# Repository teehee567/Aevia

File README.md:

# Aevia

Aevia is a DIY, battery powered lap timer and track data logger. The current hardware is the V2 Mini, a compact board that combines multi-band GNSS, a 6-axis IMU, local storage, a display interface, physical controls, and wireless connectivity.

Uses very very high end sensors, UM980, SCH16T-K01

The goal is to build something in the same general space as a Garmin Catalyst, but at a lower cost and with more control over the hardware, raw data, and software. Recorded data should also remain useful outside the device, with export to proper desktop analysis tools.

## V2 Mini hardware

The V2 Mini is built around:

- `ESP32-S31-WROOM-3-N16R16V` as the main processor and radio
- `UM980` multi-band, multi-constellation GNSS receiver
- `SCH16T-K01-1` 6-axis accelerometer and gyroscope
- microSD storage over 4-bit SDIO
- a 24-pin SPI display interface for the Adafruit 4520
- four UI buttons and four RGB status LEDs
- native USB data and USB-C power
- a 1-cell battery charger, fuel gauge, and push-button power control

See [v2_mini_design.md](./v2_mini_design.md) for the block diagrams, power tree, fitted parts, and current one-off build estimate.

## Firmware and software plan

The [base firmware](./firmware/README.md) provides structured hardware bring-up
and a button-free J6 USB inactive-slot updater. Build from `firmware/` with
`cargo build --release --locked`; use the host decoder and `board_check.py` to
upload an application image and retain its diagnostics. The
[evaluation procedure](./firmware/docs/evaluation.md) gives the repeatable
stationary bench, USB fault and recovery checks.

The immediate work is hardware bring-up and the basic firmware needed to read the GNSS and IMU, store sessions on the microSD card, and exercise the display and controls. The application backlog currently looks like this.

### High priority

- [ ] Delta T lap timing with colour coding
- [ ] Raw-data analysis that can support lap times reported to 0.001 seconds and show the limits of the hardware
- [ ] Export to Harry's LapTimer or another tool that accepts the recorded data

### Medium priority

- [ ] G-G diagram, with filtering suitable for noisy IMU output
- [ ] Automatic track detection
  - [ ] Track learning mode
  - [ ] Manual start and finish line setup
- [ ] Smart battery management
- [ ] Theoretical best lap time
- [ ] Automatic recording based on acceleration
- [ ] Sector splits for tracks that support them

### Low priority

- [ ] Configurable LED bar
- [ ] Customisable gauges
- [ ] Colour themes

### Stretch ideas

- [ ] CAN bus or OBD data logging for brake, throttle, and other vehicle data
- [ ] Bluetooth support through the ESP32
  - [ ] RTK corrections, with a target of roughly 50 Hz and centimetre-level positioning
  - [ ] Firmware updates over Bluetooth
- [ ] Action camera synchronisation

## Why the UM980

Of the modules considered, the UM980 is the best fit I found for raw GNSS quality at this price. It can output at 20 Hz while using multiple GNSS constellations. That matters in a car because an antenna inside the windscreen loses much of its view behind the metal roof. Combining GPS, GLONASS, Galileo, and BeiDou leaves more satellites available for each fix and can improve accuracy when the view of the sky is limited. A receiver advertised as "multi-GNSS" does not necessarily support its maximum update rate while using several constellations at once.

It also supports multiple frequency bands. A single-band receiver has a harder time separating a direct signal from one reflected by the car or nearby barriers. Comparing L1 with L2 or L5 gives the receiver more information for rejecting poor measurements.

The planned BT-T076 is a wide multi-band active helical antenna, although its sheet does not explicitly document every UM980 signal. Helical designs generally tolerate tilt and an uncertain ground plane better than conventional patches, but the BT-T076 datasheet does not publish the angular, per-band patterns needed to rank it against a particular patch. A correctly integrated patch that covers every required band may provide cleaner measurements in a fixed installation; many common patches are only L1 or depend on a specific ground plane. See [the GNSS antenna decision note](./gnss_antenna_design.md) for the mounting scenarios, electrical constraints, expected data effects, and A/B test plan.

The expected gain over a decent off-the-shelf logger is not enormous, and software quality will matter just as much as the receiver. For absolute lap-time proof, a track transponder still wins.

### Receivers considered

These figures are working notes from the module research and should be checked again before buying parts.

| Receiver | Notes |
|---|---|
| Unicore `UM980` | L1, L2/L5, and L6; multi-constellation; full RTK; 20 Hz with full multi-GNSS; about 50 Hz in RTK mode; roughly A$130 |
| u-blox `NEO-M9N` | L1-only; multi-constellation; 25 Hz with one constellation or 10 Hz with several; roughly A$20 |
| u-blox `NEO-M10S` | L1-only; multi-constellation; 25 Hz with one constellation or 10 Hz with several; roughly A$20 |
| u-blox `ZED-F9P` | L1 and L2; multi-constellation; full RTK; about 8 Hz with everything enabled or 20 Hz with a reduced configuration; roughly A$130 |
| Quectel `LC29H-DA/EA` | L1 and L5; multi-constellation; RTK on the EA variant; 10 Hz maximum |
| Septentrio `mosaic-X5` | All bands and constellations; the best raw quality in this comparison; capable of 100 Hz; more than A$1,000 |
| SkyTraq `PX1122R` | L1 and L2; multi-constellation RTK; apparently up to 20 Hz, although documentation and pricing were difficult to find |

The Dragy Pro was the only off-the-shelf product for which I could identify the receiver module. It uses a u-blox NEO-M10S and is listed in the research as 10 Hz with multiple constellations or 20 Hz with one. I have not found a module that clearly delivers 25 Hz, multi-GNSS, and 10 cm accuracy at the same time, so similar product claims are unlikely to be real.

The longer comparison is in [data/gps_module_research.md](./data/gps_module_research.md).
And raw GNSS modules specs are in [data/GNSS_research.xlsx](./data/GNSS_research.xlsx).

## Repository map

- [V2 Mini design notes](./v2_mini_design.md)
- [GNSS helix-versus-patch and dashboard placement analysis](./gnss_antenna_design.md)
- [V2 Mini KiCad project](./hardware/v2_mini_pcb/v2_mini.kicad_pro)
- [V2 Mini root schematic](./hardware/v2_mini_pcb/v2_mini.kicad_sch)
- [V2 Mini PCB layout](./hardware/v2_mini_pcb/v2_mini.kicad_pcb)
- [V2 Mini production BOM](./hardware/v2_mini_pcb/production/digikey_bom.csv)
- [GNSS module research](./data/gps_module_research.md)
- [V1 PCB files](./hardware/v1_pcb/)
- [Earlier full-size V2 design notes](./v2_design.md)

## Building it

I do not recommend this as a first electronics build. Several parts need reflow equipment or a capable hot-air setup, and a one off board involves a fair amount of tooling and rework cost. The V2 Mini estimate is about $500AUD for the PCB, stencil, parts, GNSS receiver, antenna, and battery.

## V1 archive

archive, old, bad

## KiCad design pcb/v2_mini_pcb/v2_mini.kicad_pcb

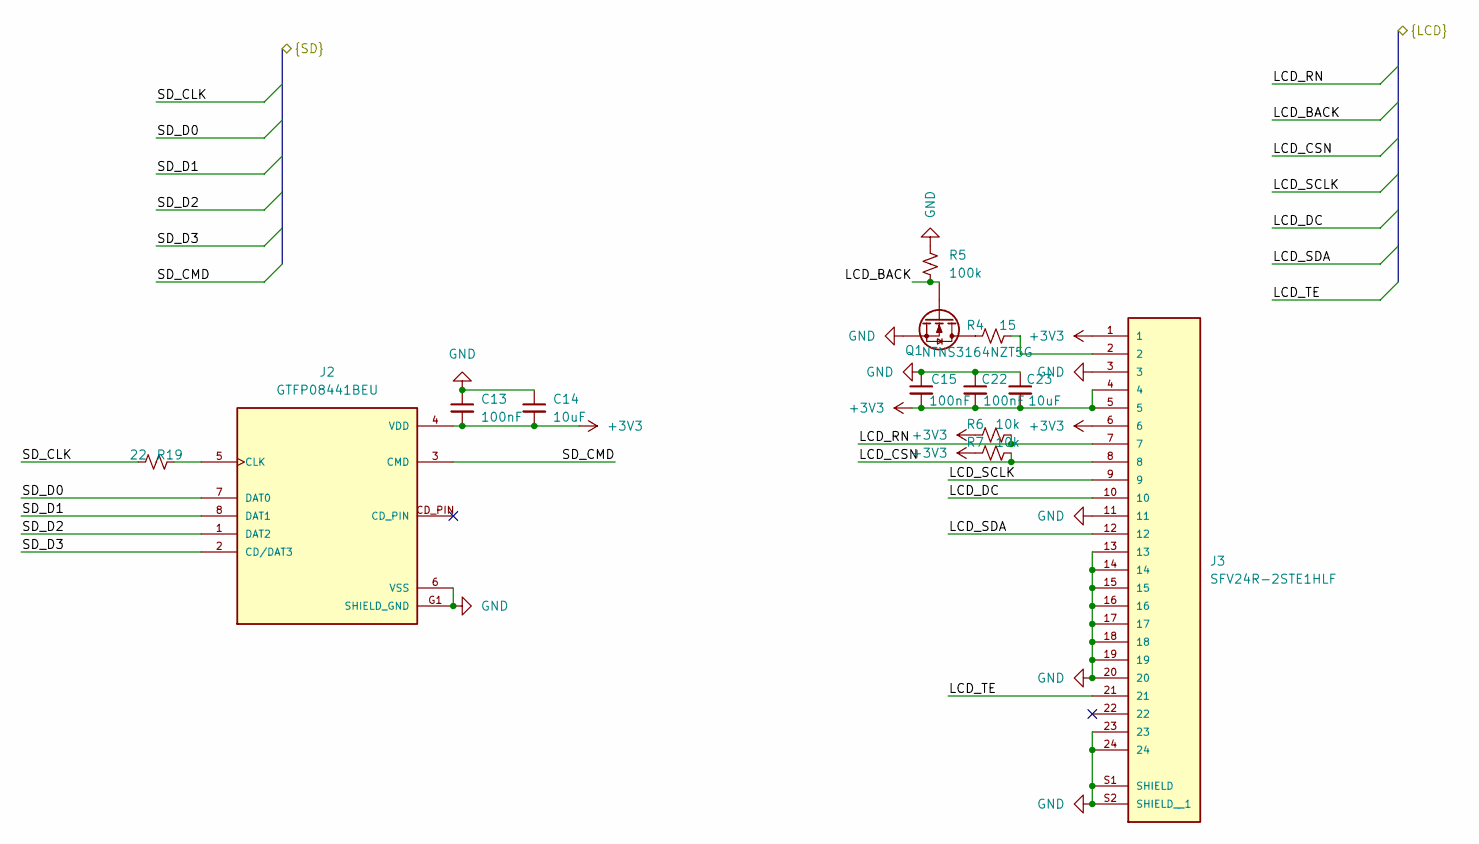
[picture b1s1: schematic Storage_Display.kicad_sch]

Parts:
C13, C15, C22: 100nF; C_0402_1005Metric; Voltage 16V; Tolerance 10%; MPN CL05B104KO5NNNC; LCSC C1525
C14, C23: 10uF; C_0603_1608Metric; Voltage 10V; Tolerance 10%; MPN CL10A106KP8NNND; DigiKey_PN 1276-CL10A106KP8NNNDCT-ND
J2: GTFP08441BEU; AMPHENOL_GTFP08441BEU; PARTREV F
J3: SFV24R-2STE1HLF; AMPHENOL_SFV24R-2STE1HLF; PARTREV C
Q1: NTNS3164NZT5G; SOT-883; MPN NTNS3164NZT5G
R4: 15; R_0402_1005Metric; MPN RC0402FR-0715RL
R5: 100k; R_0402_1005Metric; Voltage 50V; Tolerance 1%; MPN RC0402FR-07100KL; DigiKey_PN 311-100KLRCT-ND
R6, R7: 10k; R_0402_1005Metric; Voltage 50V; Tolerance 1%; MPN RC0402FR-0710KL; DigiKey_PN 311-10.0KLRCT-ND
R19: 22; R_0402_1005Metric; Voltage 50V; Tolerance 1%; MPN RC0402FR-0722RL; DigiKey_PN 311-22.0LRCT-ND

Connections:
+3V3: C13.2, C14.2, C15.2, C22.2, C23.2, J2.4 (VDD), J3.1, J3.4, J3.5, J3.6, R6.1, R7.1; also elsewhere on the board
/ESP32-S31 MCU/LCD_BACK: Q1.1 (G), R5.2; also elsewhere on the board
/ESP32-S31 MCU/LCD_CSN: J3.8, R7.2; also elsewhere on the board
/ESP32-S31 MCU/LCD_DC: J3.10; also elsewhere on the board
/ESP32-S31 MCU/LCD_RN: J3.7, R6.2; also elsewhere on the board
/ESP32-S31 MCU/LCD_SCLK: J3.9; also elsewhere on the board
/ESP32-S31 MCU/LCD_SDA: J3.12; also elsewhere on the board
/ESP32-S31 MCU/LCD_TE: J3.21; also elsewhere on the board
/ESP32-S31 MCU/SD_CLK: R19.1; also elsewhere on the board
/ESP32-S31 MCU/SD_CMD: J2.3 (CMD); also elsewhere on the board
/ESP32-S31 MCU/SD_D0: J2.7 (DAT0); also elsewhere on the board
/ESP32-S31 MCU/SD_D1: J2.8 (DAT1); also elsewhere on the board
/ESP32-S31 MCU/SD_D2: J2.1 (DAT2); also elsewhere on the board
/ESP32-S31 MCU/SD_D3: J2.2 (CD/DAT3); also elsewhere on the board
GND: C13.1, C14.1, C15.1, C22.1, C23.1, J2.6 (VSS), J2.G1 (SHIELD_GND), J2.G2 (SHIELD_GND), J2.G3 (SHIELD_GND), J3.3, J3.11, J3.13, J3.14, J3.15, J3.16, J3.17, J3.18, J3.19, J3.20, J3.23, J3.24, J3.S1 (SHIELD), J3.S2 (SHIELD__1), Q1.2 (S), R5.1; also elsewhere on the board
unnamed: J2.5 (CLK), R19.2
unnamed: J3.2, R4.2
unnamed: Q1.3 (D), R4.1

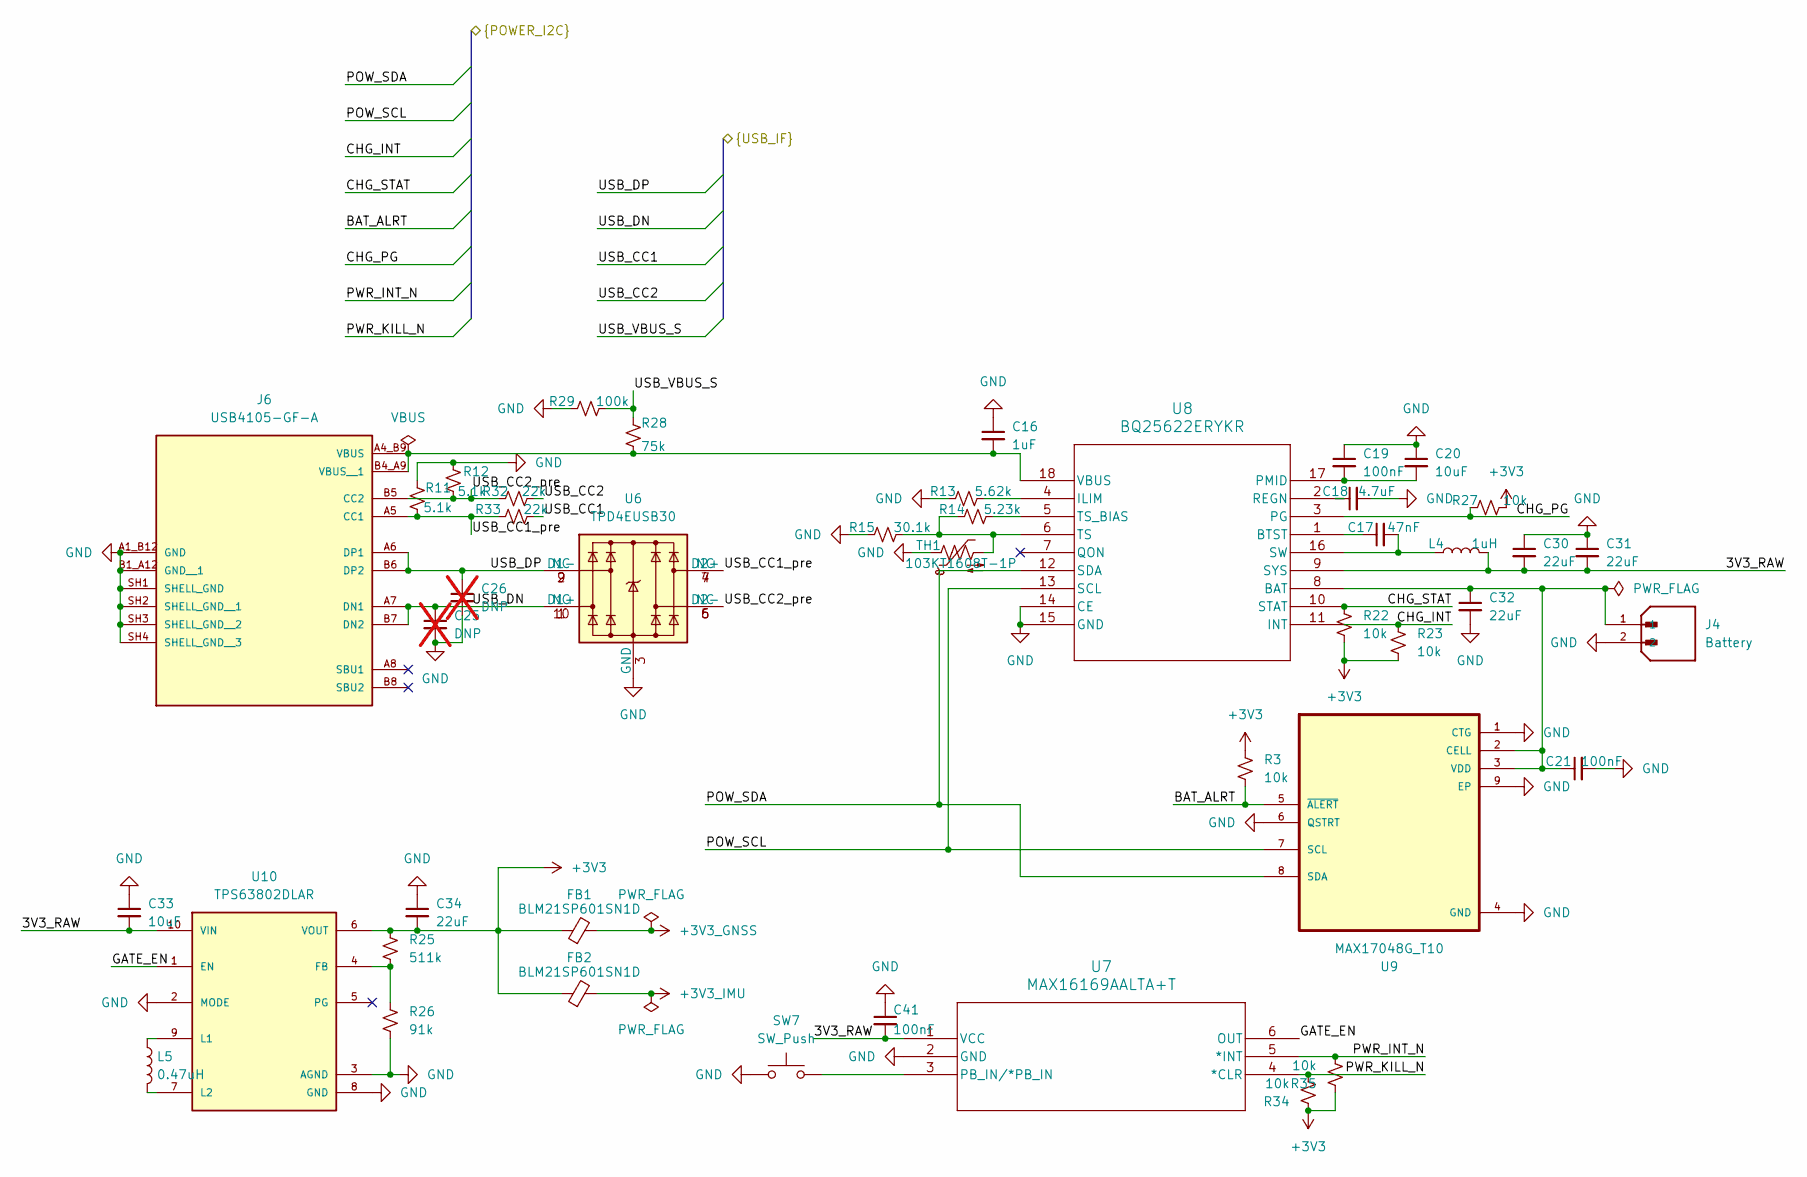
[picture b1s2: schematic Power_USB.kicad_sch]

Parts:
C16: 1uF; C_0603_1608Metric; Voltage 35V; Tolerance 10%; MPN MCASG168AB7105KTNA01; DigiKey_PN 587-MCASG168AB7105KTNA01CT-ND
C17: 47nF; C_0402_1005Metric; Voltage 25V; Tolerance 10%; MPN GRM155R71E473KA88D; DigiKey_PN 490-3254-1-ND
C18: 4.7uF; C_0603_1608Metric; Voltage 25V; Tolerance 10%; MPN GRM188R61E475KE11D; DigiKey_PN 490-7203-1-ND
C19: 100nF; C_0402_1005Metric; Voltage 50V; Tolerance 10%; MPN CL05B104KB54PNC; LCSC C307331
C20: 10uF; C_0805_2012Metric; Voltage 35V; Tolerance 10%; MPN C2012X5R1V106K125AC; DigiKey_PN 445-14418-1-ND
C21, C41: 100nF; C_0402_1005Metric; Voltage 16V; Tolerance 10%; MPN CL05B104KO5NNNC; LCSC C1525
C25, C26: DNP; C_0402_1005Metric; MPN DNP; not fitted
C30, C31, C32: 22uF; C_0805_2012Metric; Voltage 25V; Tolerance 20%; MPN CC0805MKX5R8BB226; DigiKey_PN 311-1903-1-ND
C33: 10uF; C_0603_1608Metric; Voltage 10V; Tolerance 10%; MPN CL10A106KP8NNND; DigiKey_PN 1276-CL10A106KP8NNNDCT-ND
C34: 22uF; C_0603_1608Metric; Voltage 10V; Tolerance 20%; MPN GRT188R61A226ME13D; DigiKey_PN 490-GRT188R61A226ME13DCT-ND
FB1, FB2: BLM21SP601SN1D; L_0805_2012Metric; MPN MPZ2012S601ATD25
J4: Battery; HRS_DF58-2P-1.2V_21_; PARTREV Apr.1.2022
J6: USB4105-GF-A; GCT_USB4105-GF-A; PARTREV B4
L4: 1uH; L_1008_2520Metric; MPN DFE252012F-1R0M=P2
L5: 0.47uH; L_Samsung_CIGT201610; Tolerance ±20%; MPN CIGT201610EHR47MNE; DigiKey_PN 1276-6902-1-ND
R3, R22, R23, R27, R34, R35: 10k; R_0402_1005Metric; Voltage 50V; Tolerance 1%; MPN RC0402FR-0710KL; DigiKey_PN 311-10.0KLRCT-ND
R11, R12: 5.1k; R_0402_1005Metric; Voltage 50V; Tolerance 1%; MPN RC0402FR-075K1L; DigiKey_PN 311-5.10KLRCT-ND
R13: 5.62k; R_0402_1005Metric; MPN RC0402FR-075K62L
R14: 5.23k; R_0402_1005Metric; MPN RC0402FR-075K23L
R15: 30.1k; R_0402_1005Metric; MPN CRCW040230K1FKED
R25: 511k; R_0603_1608Metric; MPN RC0603FR-07511KL
R26: 91k; R_0603_1608Metric; MPN RC0603FR-0791KL
R28: 75k; R_0402_1005Metric; Voltage 50V; Tolerance 1%; MPN RMCF0402FT75K0; DigiKey_PN RMCF0402FT75K0CT-ND
R29: 100k; R_0402_1005Metric; Voltage 50V; Tolerance 1%; MPN RC0402FR-07100KL; DigiKey_PN 311-100KLRCT-ND
R32, R33: 22k; R_0402_1005Metric; Voltage 50V; Tolerance 1%; MPN RC0402FR-0722KL; DigiKey_PN 311-22.0KLRCT-ND
SW7: SW_Push; SW_SPST_B3U-1000P; MPN B3U-1000P
TH1: 103KT1608T-1P; R_0603_1608Metric; MPN NCU18XH103F60RB
U6: TPD4EUSB30; USON-10_2.5x1.0mm_P0.5mm; MPN TPD4EUSB30DQAR
U7: MAX16169AALTA+T; 21-0164_L622&plus_1_ADI; MPN MAX16169AALTA+T
U8: BQ25622ERYKR; WQFN-HR18__RYK_TEX; MPN BQ25622ERYKR
U9: MAX17048G_T10; SON50P200X200X80-9N; MPN MAX17048G+T10
U10: TPS63802DLAR; VREG_TPS63802DLAR; PARTREV B

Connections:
+3V3: C34.2, FB1.1, FB2.1, R3.1, R22.2, R23.2, R25.1, R27.2, R34.1, R35.1, U10.6 (VOUT); also elsewhere on the board
+3V3_GNSS: FB1.2; also elsewhere on the board
+3V3_IMU: FB2.2; also elsewhere on the board
/ESP32-S31 MCU/BAT_ALRT: R3.2, U9.5 (~ALERT); also elsewhere on the board
/ESP32-S31 MCU/CHG_INT: R23.1, U8.11 (INT); also elsewhere on the board
/ESP32-S31 MCU/CHG_PG: R27.1, U8.3 (PG); also elsewhere on the board
/ESP32-S31 MCU/CHG_STAT: R22.1, U8.10 (STAT); also elsewhere on the board
/ESP32-S31 MCU/POW_SCL: U8.13 (SCL), U9.7 (SCL); also elsewhere on the board
/ESP32-S31 MCU/POW_SDA: U8.12 (SDA), U9.8 (SDA); also elsewhere on the board
/ESP32-S31 MCU/PWR_INT_N: R35.2, U7.5 (*INT); also elsewhere on the board
/ESP32-S31 MCU/PWR_KILL_N: R34.2, U7.4 (*CLR); also elsewhere on the board
/ESP32-S31 MCU/USB_CC1: R33.2; also elsewhere on the board
/ESP32-S31 MCU/USB_CC2: R32.2; also elsewhere on the board
/ESP32-S31 MCU/USB_DN: C25.1, J6.A7 (DN1), J6.B7 (DN2), U6.1 (D1+), U6.10 (NC); also elsewhere on the board
/ESP32-S31 MCU/USB_DP: C26.1, J6.A6 (DP1), J6.B6 (DP2), U6.2 (D1-), U6.9 (NC); also elsewhere on the board
/ESP32-S31 MCU/USB_VBUS_S: R28.1, R29.2; also elsewhere on the board
/Power + USB/3V3_RAW: C30.2, C31.2, C33.2, C41.2, L4.2, U7.1 (VCC), U8.9 (SYS), U10.10 (VIN)
/Power + USB/GATE_EN: U7.6 (OUT), U10.1 (EN)
/Power + USB/USB_CC1_pre: J6.A5 (CC1), R11.2, R33.1, U6.4 (D2+), U6.7 (NC)
/Power + USB/USB_CC2_pre: J6.B5 (CC2), R12.2, R32.1, U6.5 (D2-), U6.6 (NC)
GND: C16.1, C18.2, C19.1, C20.1, C21.2, C25.2, C26.2, C30.1, C31.1, C32.2, C33.1, C34.1, C41.1, J4.2, J6.A1_B12 (GND), J6.B1_A12 (GND__1), J6.SH1 (SHELL_GND), J6.SH2 (SHELL_GND__1), J6.SH3 (SHELL_GND__2), J6.SH4 (SHELL_GND__3), R11.1, R12.1, R13.1, R15.1, R26.2, R29.1, SW7.1, TH1.1, U6.3 (GND), U6.8 (GND), U7.2 (GND), U8.14 (CE), U8.15 (GND), U9.1 (CTG), U9.4 (GND), U9.6 (QSTRT), U9.9 (EP), U10.2 (MODE), U10.3 (AGND), U10.8 (GND); also elsewhere on the board
unnamed: C16.2, J6.A4_B9 (VBUS), J6.B4_A9 (VBUS__1), R28.2, U8.18 (VBUS)
unnamed: SW7.2, U7.3 (PB_IN/*PB_IN)
unnamed: C21.1, C32.1, J4.1, U8.8 (BAT), U9.2 (CELL), U9.3 (VDD)
unnamed: C17.1, U8.1 (BTST)
unnamed: R13.2, U8.4 (ILIM)
unnamed: C19.2, C20.2, U8.17 (PMID)
unnamed: C18.1, U8.2 (REGN)
unnamed: C17.2, L4.1, U8.16 (SW)
unnamed: R14.1, R15.2, TH1.2, U8.6 (TS)
unnamed: R14.2, U8.5 (TS_BIAS)
unnamed: R25.2, R26.1, U10.4 (FB)
unnamed: L5.1, U10.9 (L1)
unnamed: L5.2, U10.7 (L2)

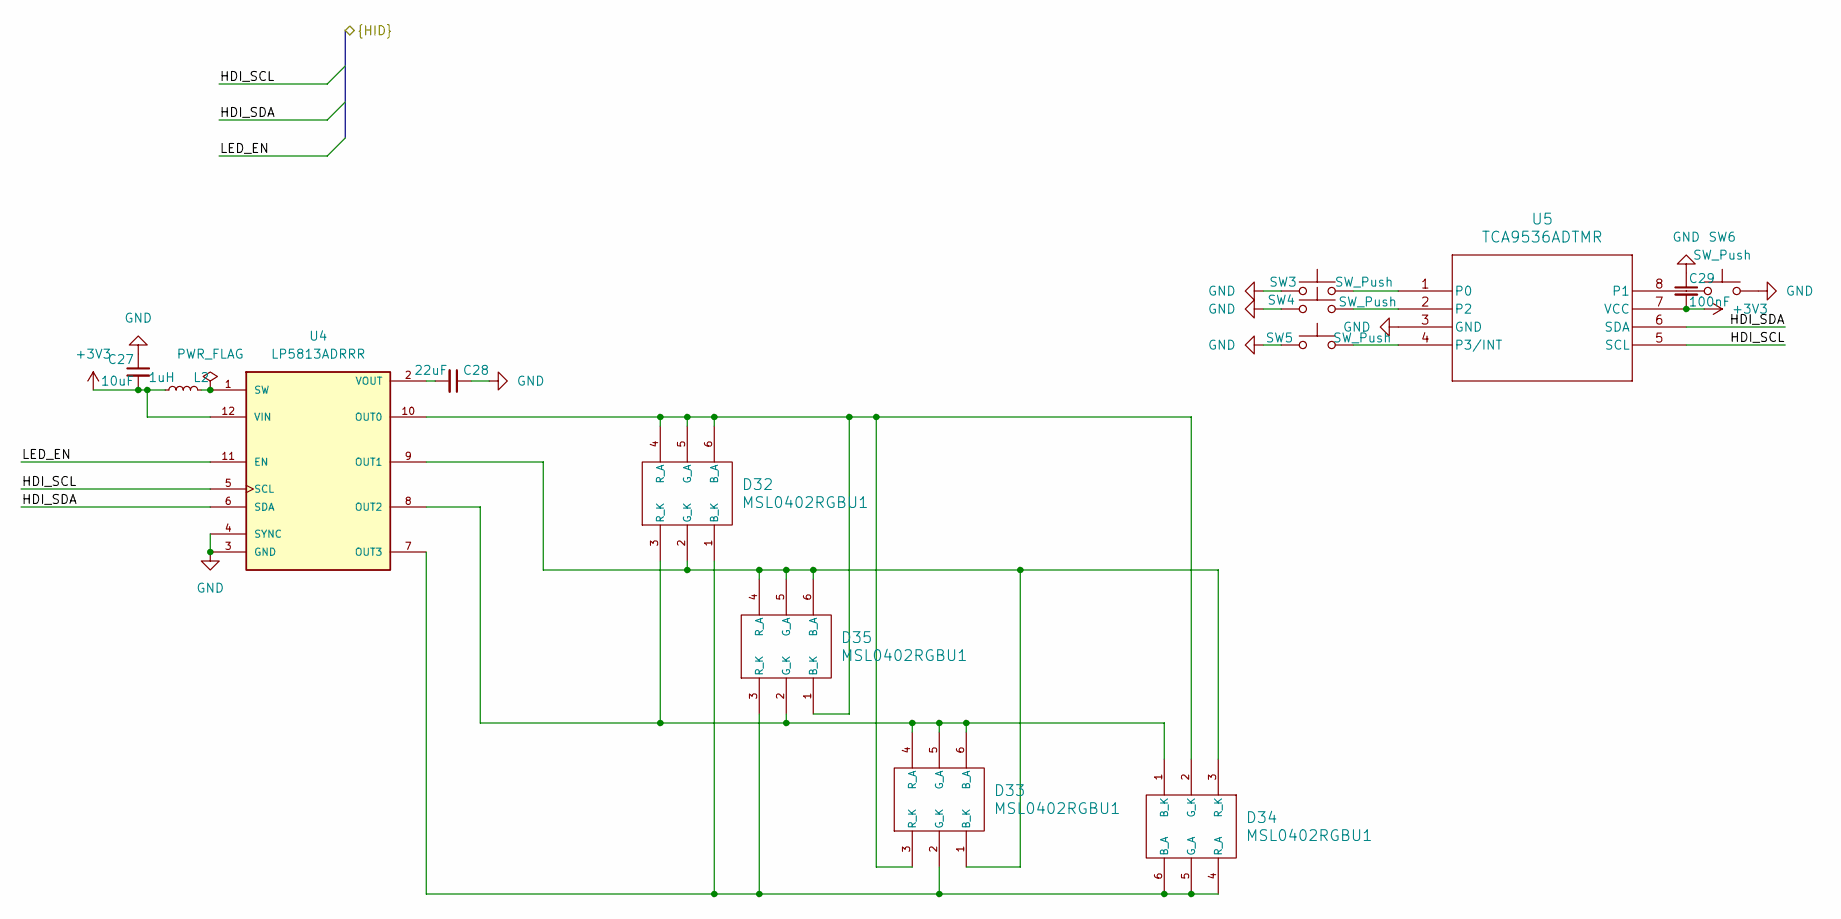
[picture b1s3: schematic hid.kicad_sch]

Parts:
C27: 10uF; C_0603_1608Metric; Voltage 10V; Tolerance 10%; MPN CL10A106KP8NNND; DigiKey_PN 1276-CL10A106KP8NNNDCT-ND
C28: 22uF; C_0805_2012Metric; Voltage 25V; Tolerance 20%; MPN CC0805MKX5R8BB226; DigiKey_PN 311-1903-1-ND
C29: 100nF; C_0402_1005Metric; MPN CL05B104KO5NNNC
D32, D33, D34, D35: MSL0402RGBU1; LED_MSL04_ROM; MPN MSL0402RGBU1
L2: 1uH; L_1008_2520Metric; MPN DFE252012F-1R0M=P2
SW3, SW4, SW5, SW6: SW_Push; SW_SPST_B3U-1000P; MPN B3U-1000P
U4: LP5813ADRRR; IC_LP5813ADRRR; PARTREV C
U5: TCA9536ADTMR; X2SON8_DTM_TEX; MPN TCA9536ADTMR

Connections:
+3V3: C27.2, C29.2, L2.2, U4.12 (VIN), U5.7 (VCC); also elsewhere on the board
/ESP32-S31 MCU/LED_EN: U4.11 (EN); also elsewhere on the board
/ESP32-S31 MCU/POW_SCL: U4.5 (SCL), U5.5 (SCL); also elsewhere on the board
/ESP32-S31 MCU/POW_SDA: U4.6 (SDA), U5.6 (SDA); also elsewhere on the board
GND: C27.1, C28.1, C29.1, SW3.1, SW4.1, SW5.1, SW6.2, U4.3 (GND), U4.4 (SYNC), U4.13 (GND), U5.3 (GND); also elsewhere on the board
unnamed: D32.4 (R_A), D32.5 (G_A), D32.6 (B_A), D33.3 (R_K), D34.2 (G_K), D35.1 (B_K), U4.10 (OUT0)
unnamed: D32.1 (B_K), D33.2 (G_K), D34.4 (R_A), D34.5 (G_A), D34.6 (B_A), D35.3 (R_K), U4.7 (OUT3)
unnamed: D32.2 (G_K), D33.1 (B_K), D34.3 (R_K), D35.4 (R_A), D35.5 (G_A), D35.6 (B_A), U4.9 (OUT1)
unnamed: D32.3 (R_K), D33.4 (R_A), D33.5 (G_A), D33.6 (B_A), D34.1 (B_K), D35.2 (G_K), U4.8 (OUT2)
unnamed: L2.1, U4.1 (SW)
unnamed: C28.2, U4.2 (VOUT)
unnamed: SW3.2, U5.1 (P0)
unnamed: SW6.1, U5.8 (P1)
unnamed: SW4.2, U5.2
unnamed: SW5.2, U5.4 (P3/INT)

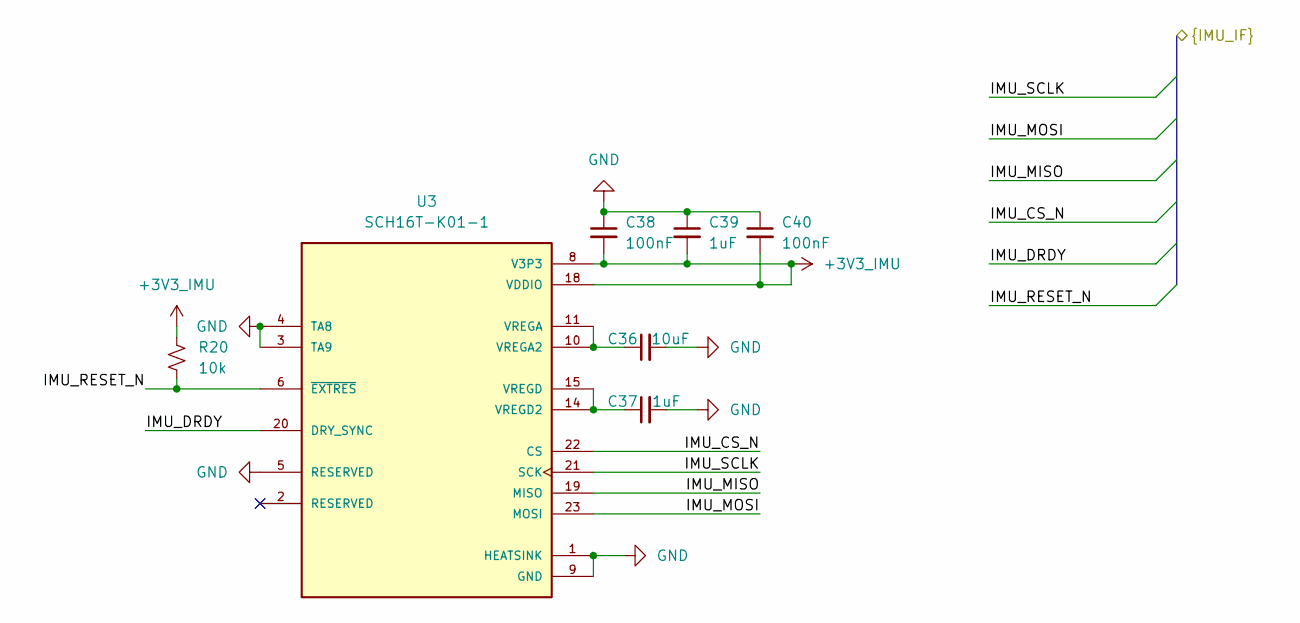
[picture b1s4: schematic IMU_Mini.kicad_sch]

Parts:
C36: 10uF; C_0603_1608Metric; Voltage 10V; Tolerance 10%; MPN CL10A106KP8NNND; DigiKey_PN 1276-CL10A106KP8NNNDCT-ND
C37, C39: 1uF; C_0402_1005Metric; Voltage 25V; Tolerance 10%; MPN CL05A105KA5NQNC; LCSC C52923
C38, C40: 100nF; C_0402_1005Metric; Voltage 16V; Tolerance 10%; MPN CL05B104KO5NNNC; LCSC C1525
R20: 10k; R_0402_1005Metric; Voltage 50V; Tolerance 1%; MPN RC0402FR-0710KL; DigiKey_PN 311-10.0KLRCT-ND
U3: SCH16T-K01-1; XDCR_SCH16T-K01-1; PARTREV 6

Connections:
+3V3_IMU: C38.2, C39.2, C40.2, R20.1, U3.8 (V3P3), U3.17 (V3P3), U3.18 (VDDIO); also elsewhere on the board
/ESP32-S31 MCU/IMU_CS_N: U3.22 (CS); also elsewhere on the board
/ESP32-S31 MCU/IMU_DRDY: U3.20 (DRY_SYNC); also elsewhere on the board
/ESP32-S31 MCU/IMU_MISO: U3.19 (MISO); also elsewhere on the board
/ESP32-S31 MCU/IMU_MOSI: U3.23 (MOSI); also elsewhere on the board
/ESP32-S31 MCU/IMU_RESET_N: R20.2, U3.6 (~EXTRES); also elsewhere on the board
/ESP32-S31 MCU/IMU_SCLK: U3.21 (SCK); also elsewhere on the board
GND: C36.2, C37.2, C38.1, C39.1, C40.1, U3.1 (HEATSINK), U3.3 (TA9), U3.4 (TA8), U3.5 (RESERVED), U3.7 (RESERVED), U3.9 (GND), U3.12 (GND), U3.13 (GND), U3.16 (GND), U3.24 (HEATSINK); also elsewhere on the board
unnamed: C36.1, U3.10 (VREGA2), U3.11 (VREGA)
unnamed: C37.1, U3.14 (VREGD2), U3.15 (VREGD)

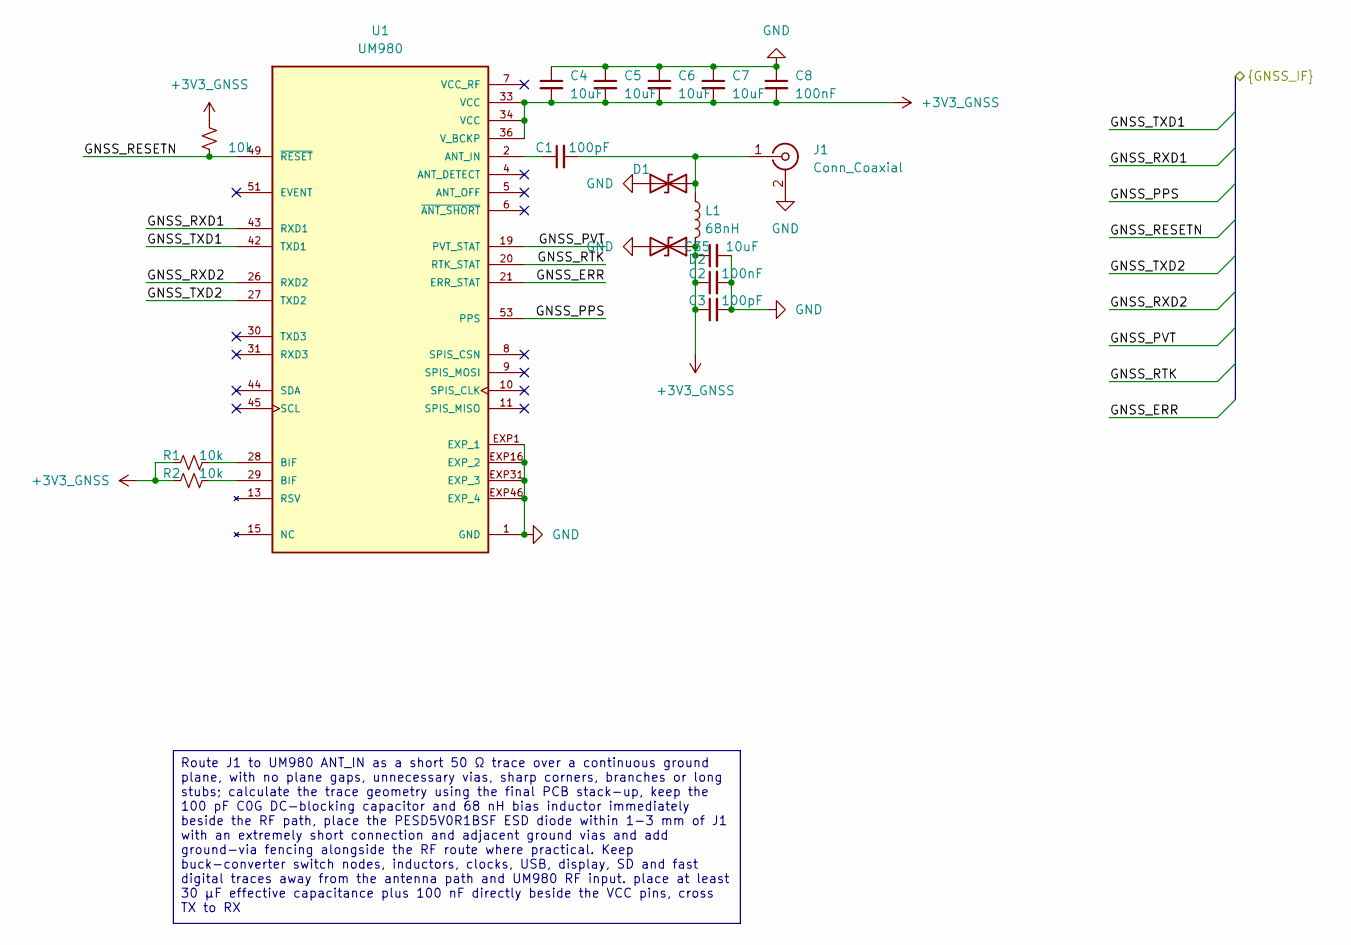
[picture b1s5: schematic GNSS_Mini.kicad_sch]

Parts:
C1, C3: 100pF; C_0402_1005Metric; Voltage 50V; Tolerance 5%; MPN GRM1555C1H101JA01D; DigiKey_PN 490-5922-1-ND
C2, C8: 100nF; C_0402_1005Metric; Voltage 16V; Tolerance 10%; MPN CL05B104KO5NNNC; LCSC C1525
C4, C5, C6, C7, C35: 10uF; C_0805_2012Metric; Voltage 35V; Tolerance 10%; MPN C2012X5R1V106K125AC; DigiKey_PN 445-14418-1-ND
D1: Texas_DPY0002A_0.6x1mm_P0.65mm; MPN TPD1E0B04DPYR
D2: D_SOD-323F; MPN ESDS311DYFR
J1: Conn_Coaxial; U.FL_Hirose_U.FL-R-SMT-1_Vertical; MPN U.FL-R-SMT-1(01)
L1: 68nH; L_0603_1608Metric; MPN LQW18AN68NJ00D
R1, R2, R24: 10k; R_0402_1005Metric; Voltage 50V; Tolerance 1%; MPN RC0402FR-0710KL; DigiKey_PN 311-10.0KLRCT-ND
U1: UM980; XCVR_UM980; PARTREV R1.9

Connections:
+3V3_GNSS: C2.1, C3.1, C4.2, C5.2, C6.2, C7.2, C8.2, C35.1, D2.1 (A1), L1.2, R1.1, R2.1, R24.2, U1.33 (VCC), U1.34 (VCC), U1.36 (V_BCKP); also elsewhere on the board
/ESP32-S31 MCU/GNSS_ERR: U1.21 (ERR_STAT); also elsewhere on the board
/ESP32-S31 MCU/GNSS_PPS: U1.53 (PPS); also elsewhere on the board
/ESP32-S31 MCU/GNSS_PVT: U1.19 (PVT_STAT); also elsewhere on the board
/ESP32-S31 MCU/GNSS_RESETN: R24.1, U1.49 (~RESET); also elsewhere on the board
/ESP32-S31 MCU/GNSS_RTK: U1.20 (RTK_STAT); also elsewhere on the board
/ESP32-S31 MCU/GNSS_RXD1: U1.43 (RXD1); also elsewhere on the board
/ESP32-S31 MCU/GNSS_RXD2: U1.26 (RXD2); also elsewhere on the board
/ESP32-S31 MCU/GNSS_TXD1: U1.42 (TXD1); also elsewhere on the board
/ESP32-S31 MCU/GNSS_TXD2: U1.27 (TXD2); also elsewhere on the board
GND: C2.2, C3.2, C4.1, C5.1, C6.1, C7.1, C8.1, C35.2, D1.1 (A1), D2.2 (A2), J1.2 (Ext), U1.1 (GND), U1.3 (GND), U1.12 (GND), U1.14 (GND), U1.32 (GND), U1.37 (GND), U1.41 (GND), U1.48 (GND), U1.EXP1 (EXP_1), U1.EXP2 (EXP_1), U1.EXP3 (EXP_1), U1.EXP4 (EXP_1), U1.EXP5 (EXP_1), U1.EXP6 (EXP_1), U1.EXP7 (EXP_1), U1.EXP8 (EXP_1), U1.EXP9 (EXP_1), U1.EXP10 (EXP_1), U1.EXP11 (EXP_1), U1.EXP12 (EXP_1), U1.EXP13 (EXP_1), U1.EXP14 (EXP_1), U1.EXP15 (EXP_1), U1.EXP16 (EXP_2), U1.EXP17 (EXP_2), U1.EXP18 (EXP_2), U1.EXP19 (EXP_2), U1.EXP20 (EXP_2), U1.EXP21 (EXP_2), U1.EXP22 (EXP_2), U1.EXP23 (EXP_2), U1.EXP24 (EXP_2), U1.EXP25 (EXP_2), U1.EXP26 (EXP_2), U1.EXP27 (EXP_2), U1.EXP28 (EXP_2), U1.EXP29 (EXP_2), U1.EXP30 (EXP_2), U1.EXP31 (EXP_3), U1.EXP32 (EXP_3), U1.EXP33 (EXP_3), U1.EXP34 (EXP_3), U1.EXP35 (EXP_3), U1.EXP36 (EXP_3), U1.EXP37 (EXP_3), U1.EXP38 (EXP_3), U1.EXP39 (EXP_3), U1.EXP40 (EXP_3), U1.EXP41 (EXP_3), U1.EXP42 (EXP_3), U1.EXP43 (EXP_3), U1.EXP44 (EXP_3), U1.EXP45 (EXP_3), U1.EXP46 (EXP_4), U1.EXP47 (EXP_4), U1.EXP48 (EXP_4); also elsewhere on the board
unnamed: C1.2, D1.2 (A2), J1.1 (In), L1.1
unnamed: R1.2, U1.28 (BIF)
unnamed: R2.2, U1.29 (BIF)
unnamed: C1.1, U1.2 (ANT_IN)

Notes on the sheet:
Route J1 to UM980 ANT_IN as a short 50 Ω trace over a continuous ground plane, with no plane gaps, unnecessary vias, sharp corners, branches or long stubs; calculate the trace geometry using the final PCB stack-up, keep the 100 pF C0G DC-blocking capacitor and 68 nH bias inductor immediately beside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
